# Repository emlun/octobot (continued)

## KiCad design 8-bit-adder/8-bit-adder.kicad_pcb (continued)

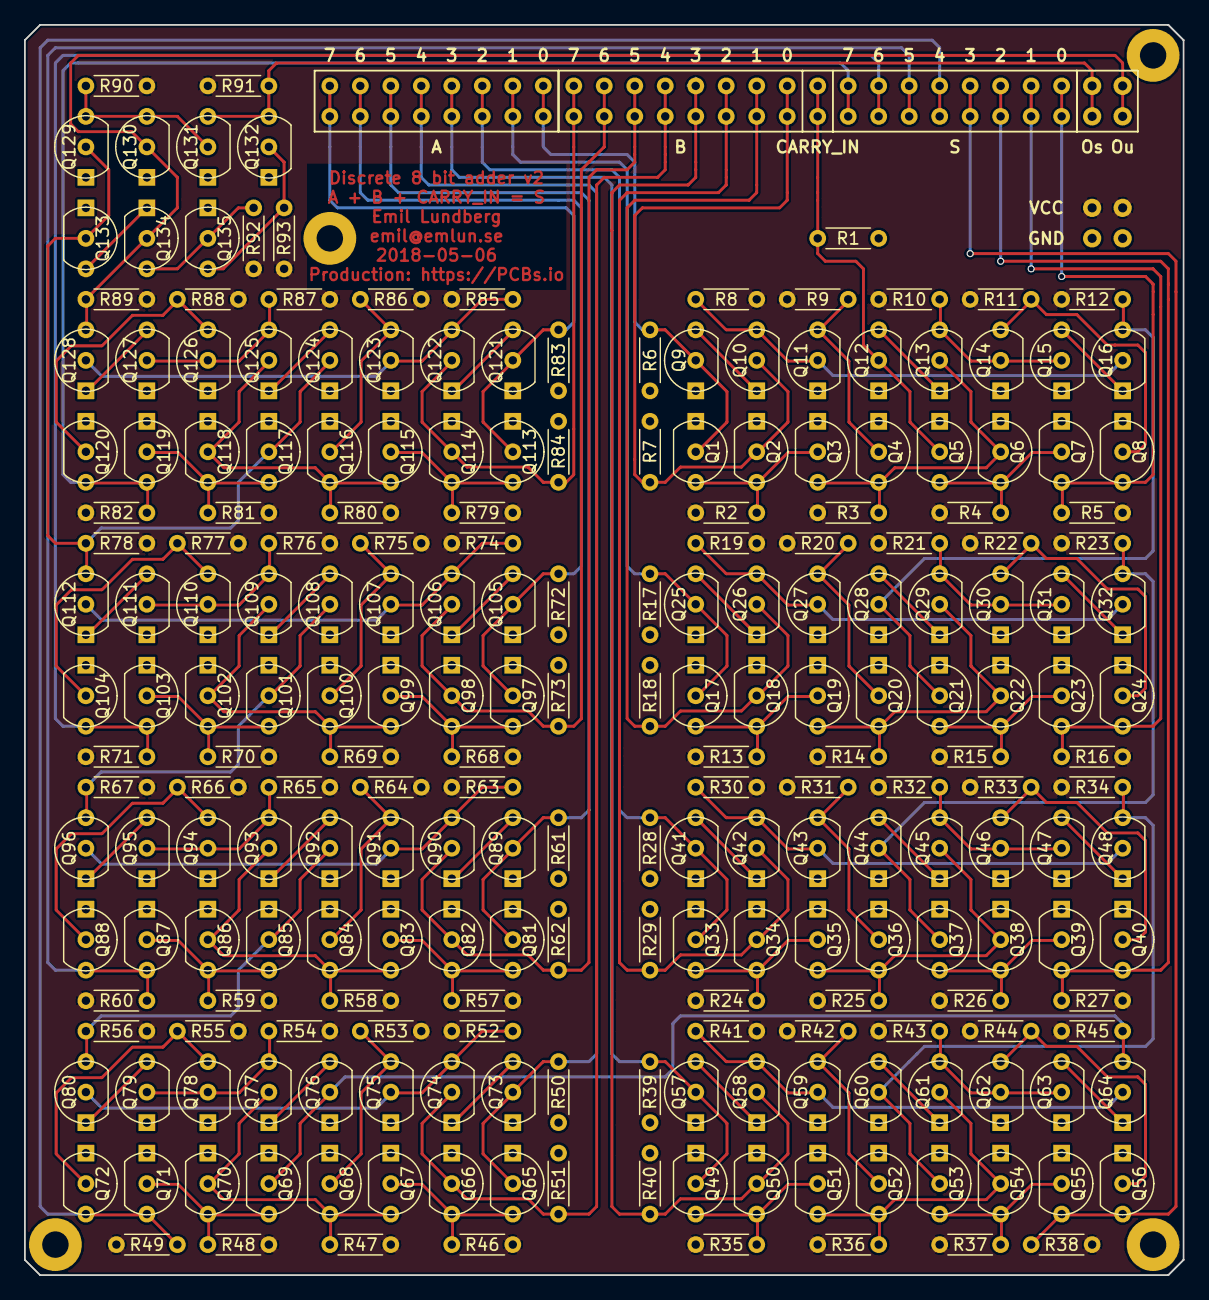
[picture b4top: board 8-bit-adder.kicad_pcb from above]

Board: 2 copper layers, 96.5 x 104.1 mm, 234 parts (0 on the bottom side), 120 nets.

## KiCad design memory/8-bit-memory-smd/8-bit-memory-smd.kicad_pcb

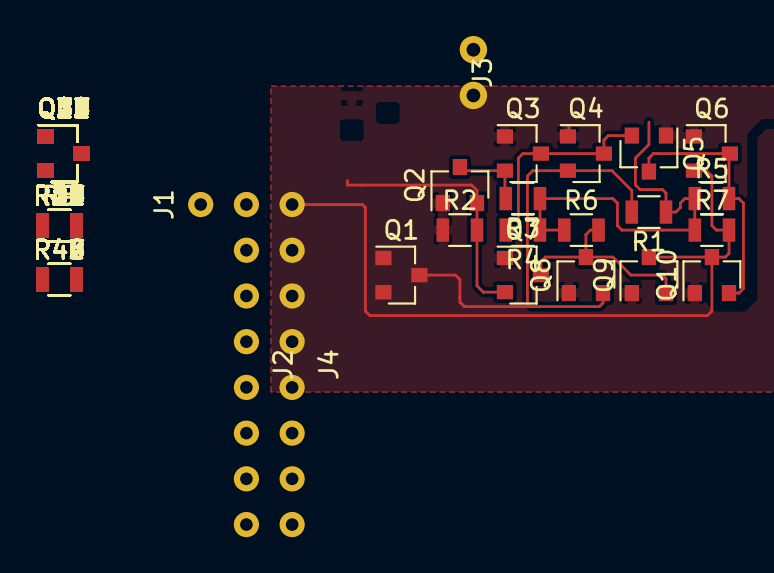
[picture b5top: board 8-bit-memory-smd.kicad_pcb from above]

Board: 2 copper layers, 126 parts (0 on the bottom side), 52 nets.

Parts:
J1: J1-1_bit_bus
J2, J4: J8-8_bit_bus_connector
J3: J2-2_pole_connector
Q1, Q2, Q3, Q4, Q5, Q6, Q7, Q8, Q9, Q10, Q11, Q12, Q13, Q14, Q15, Q16, Q17, Q18, Q19, Q20, Q21, Q22, Q23, Q24, Q25, Q26, Q27, Q28, Q29, Q30, Q31, Q32, Q33, Q34, Q35, Q36, Q37, Q38, Q39, Q40, Q41, Q42, Q43, Q44, Q45, Q46, Q47, Q48, Q49, Q50, Q51, Q52, Q53, Q54, Q55, Q56, Q57, Q58, Q59, Q60, Q61, Q62, Q63, Q64, Q65, Q66, Q67, Q68, Q69, Q70, Q71, Q72, Q73: 2N7000; SOT-23
R1, R2, R3, R4, R5, R6, R7, R8, R9, R10, R11, R12, R13, R14, R15, R16, R17, R18, R19, R20, R21, R22, R23, R24, R25, R26, R27, R28, R29, R30, R31, R32, R33, R34, R35, R36, R37, R38, R39, R40, R41, R42, R43, R44, R45, R46, R47, R48, R49: R; R_0805

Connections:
/I0: J2.0, Q2.2, Q7.2, R2.2
/I1: J2.1, Q11.2, Q16.2, R8.2
/I2: J2.2, Q20.2, Q25.2, R14.2
/I3: J2.3, Q29.2, Q34.2, R20.2
/I4: J2.4, Q38.2, Q43.2, R26.2
/I5: J2.5, Q47.2, Q52.2, R32.2
/I6: J2.6, Q56.2, Q61.2, R38.2
/I7: J2.7, Q65.2, Q70.2, R44.2
/O0: J4.0, Q6.2, Q9.3, Q10.3, R7.2
/O1: J4.1, Q15.2, Q18.3, Q19.3, R13.2
/O2: J4.2, Q24.2, Q27.3, Q28.3, R19.2
/O3: J4.3, Q33.2, Q36.3, Q37.3, R25.2
/O4: J4.4, Q42.2, Q45.3, Q46.3, R31.2
/O5: J4.5, Q51.2, Q54.3, Q55.3, R37.2
/O6: J4.6, Q60.2, Q63.3, Q64.3, R43.2
/O7: J4.7, Q69.2, Q72.3, Q73.3, R49.2
/W: J1.1, Q1.2
/notW: Q1.3, Q4.2, Q8.2, Q13.2, Q17.2, Q22.2, Q26.2, Q31.2, Q35.2, Q40.2, Q44.2, Q49.2, Q53.2, Q58.2, Q62.2, Q67.2, Q71.2, R1.2
GND: J3.1, Q1.1, Q2.1, Q3.1, Q4.1, Q5.1, Q6.1, Q7.1, Q8.1, Q9.1, Q10.1, Q11.1, Q12.1, Q13.1, Q14.1, Q15.1, Q16.1, Q17.1, Q18.1, Q19.1, Q20.1, Q21.1, Q22.1, Q23.1, Q24.1, Q25.1, Q26.1, Q27.1, Q28.1, Q29.1, Q30.1, Q31.1, Q32.1, Q33.1, Q34.1, Q35.1, Q36.1, Q37.1, Q38.1, Q39.1, Q40.1, Q41.1, Q42.1, Q43.1, Q44.1, Q45.1, Q46.1, Q47.1, Q48.1, Q49.1, Q50.1, Q51.1, Q52.1, Q53.1, Q54.1, Q55.1, Q56.1, Q57.1, Q58.1, Q59.1, Q60.1, Q61.1, Q62.1, Q63.1, Q64.1, Q65.1, Q66.1, Q67.1, Q68.1, Q69.1, Q70.1, Q71.1, Q72.1, Q73.1, R2.1, R8.1, R14.1, R20.1, R26.1, R32.1, R38.1, R44.1
unnamed: Q2.3, Q3.2, R3.2
unnamed: Q3.3, Q4.3, Q5.2, R4.2
unnamed: Q7.3, Q8.3, Q9.2, R6.2
unnamed: Q5.3, Q6.3, Q10.2, R5.2
unnamed: Q11.3, Q12.2, R9.2
unnamed: Q12.3, Q13.3, Q14.2, R10.2
unnamed: Q14.3, Q15.3, Q19.2, R11.2
unnamed: Q16.3, Q17.3, Q18.2, R12.2
unnamed: Q20.3, Q21.2, R15.2
unnamed: Q21.3, Q22.3, Q23.2, R16.2
unnamed: Q23.3, Q24.3, Q28.2, R17.2
unnamed: Q25.3, Q26.3, Q27.2, R18.2
unnamed: Q29.3, Q30.2, R21.2
unnamed: Q30.3, Q31.3, Q32.2, R22.2
unnamed: Q32.3, Q33.3, Q37.2, R23.2
unnamed: Q34.3, Q35.3, Q36.2, R24.2
unnamed: Q38.3, Q39.2, R27.2
unnamed: Q39.3, Q40.3, Q41.2, R28.2
unnamed: Q41.3, Q42.3, Q46.2, R29.2
unnamed: Q43.3, Q44.3, Q45.2, R30.2
unnamed: Q47.3, Q48.2, R33.2
unnamed: Q48.3, Q49.3, Q50.2, R34.2
unnamed: Q50.3, Q51.3, Q55.2, R35.2
unnamed: Q52.3, Q53.3, Q54.2, R36.2
unnamed: Q56.3, Q57.2, R39.2
unnamed: Q57.3, Q58.3, Q59.2, R40.2
unnamed: Q59.3, Q60.3, Q64.2, R41.2
unnamed: Q61.3, Q62.3, Q63.2, R42.2
unnamed: Q65.3, Q66.2, R45.2
unnamed: Q66.3, Q67.3, Q68.2, R46.2
unnamed: Q68.3, Q69.3, Q73.2, R47.2
unnamed: Q70.3, Q71.3, Q72.2, R48.2
VCC: J3.2, R1.1, R3.1, R4.1, R5.1, R6.1, R7.1, R9.1, R10.1, R11.1, R12.1, R13.1, R15.1, R16.1, R17.1, R18.1, R19.1, R21.1, R22.1, R23.1, R24.1, R25.1, R27.1, R28.1, R29.1, R30.1, R31.1, R33.1, R34.1, R35.1, R36.1, R37.1, R39.1, R40.1, R41.1, R42.1, R43.1, R45.1, R46.1, R47.1, R48.1, R49.1

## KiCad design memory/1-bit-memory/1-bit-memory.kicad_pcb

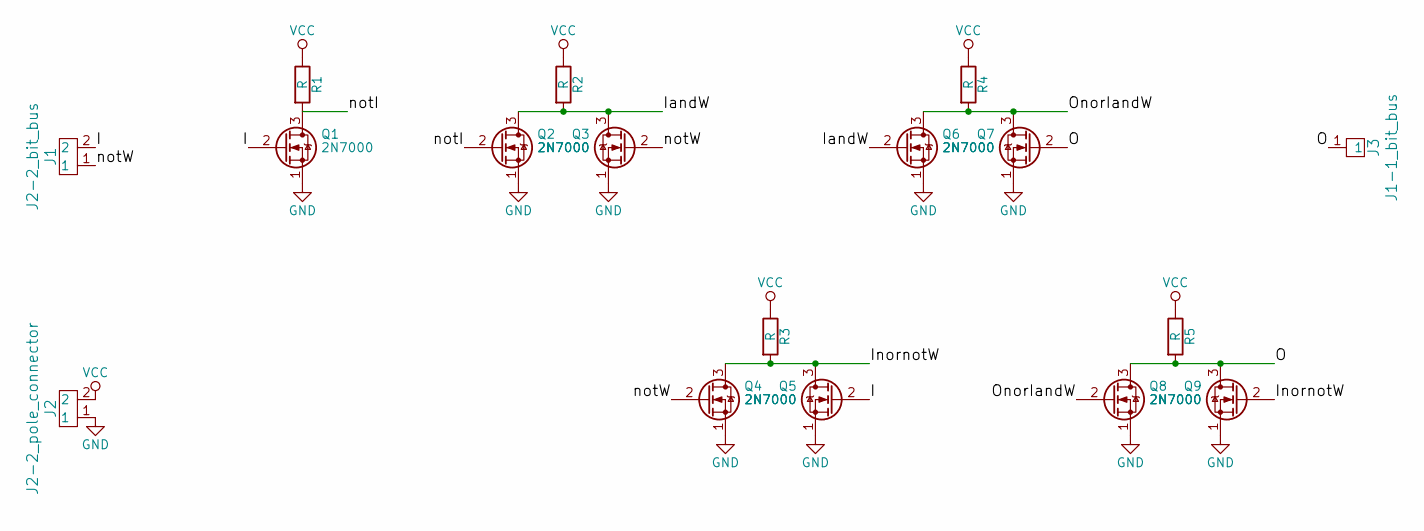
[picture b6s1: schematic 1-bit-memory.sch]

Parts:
J1: J2-2_bit_bus; J2-2_pole_connector
J2: J2-2_pole_connector
J3: J1-1_bit_bus
Q1, Q2, Q3, Q4, Q5, Q6, Q7, Q8, Q9: 2N7000; SOT-23
R1, R2, R3, R4, R5: R; R_0805

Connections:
/I: J1.2, Q1.2 (G), Q5.2 (G)
/IandW: Q2.3 (D), Q3.3 (D), Q6.2 (G), R2.2
/InornotW: Q4.3 (D), Q5.3 (D), Q9.2 (G), R3.2
/O: J3.1, Q7.2 (G), Q8.3 (D), Q9.3 (D), R5.2
/OnorIandW: Q6.3 (D), Q7.3 (D), Q8.2 (G), R4.2
/notI: Q1.3 (D), Q2.2 (G), R1.2
/notW: J1.1, Q3.2 (G), Q4.2 (G)
GND: J2.1, Q1.1 (S), Q2.1 (S), Q3.1 (S), Q4.1 (S), Q5.1 (S), Q6.1 (S), Q7.1 (S), Q8.1 (S), Q9.1 (S)
VCC: J2.2, R1.1, R2.1, R3.1, R4.1, R5.1

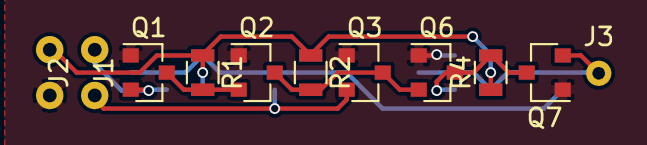
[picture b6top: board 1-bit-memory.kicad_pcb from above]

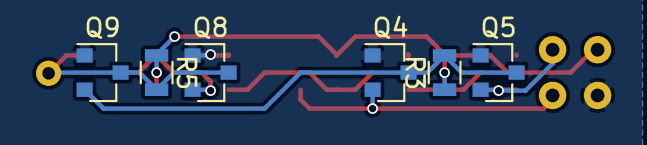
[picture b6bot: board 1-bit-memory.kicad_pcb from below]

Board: 2 copper layers, 17 parts (6 on the bottom side), 9 nets.

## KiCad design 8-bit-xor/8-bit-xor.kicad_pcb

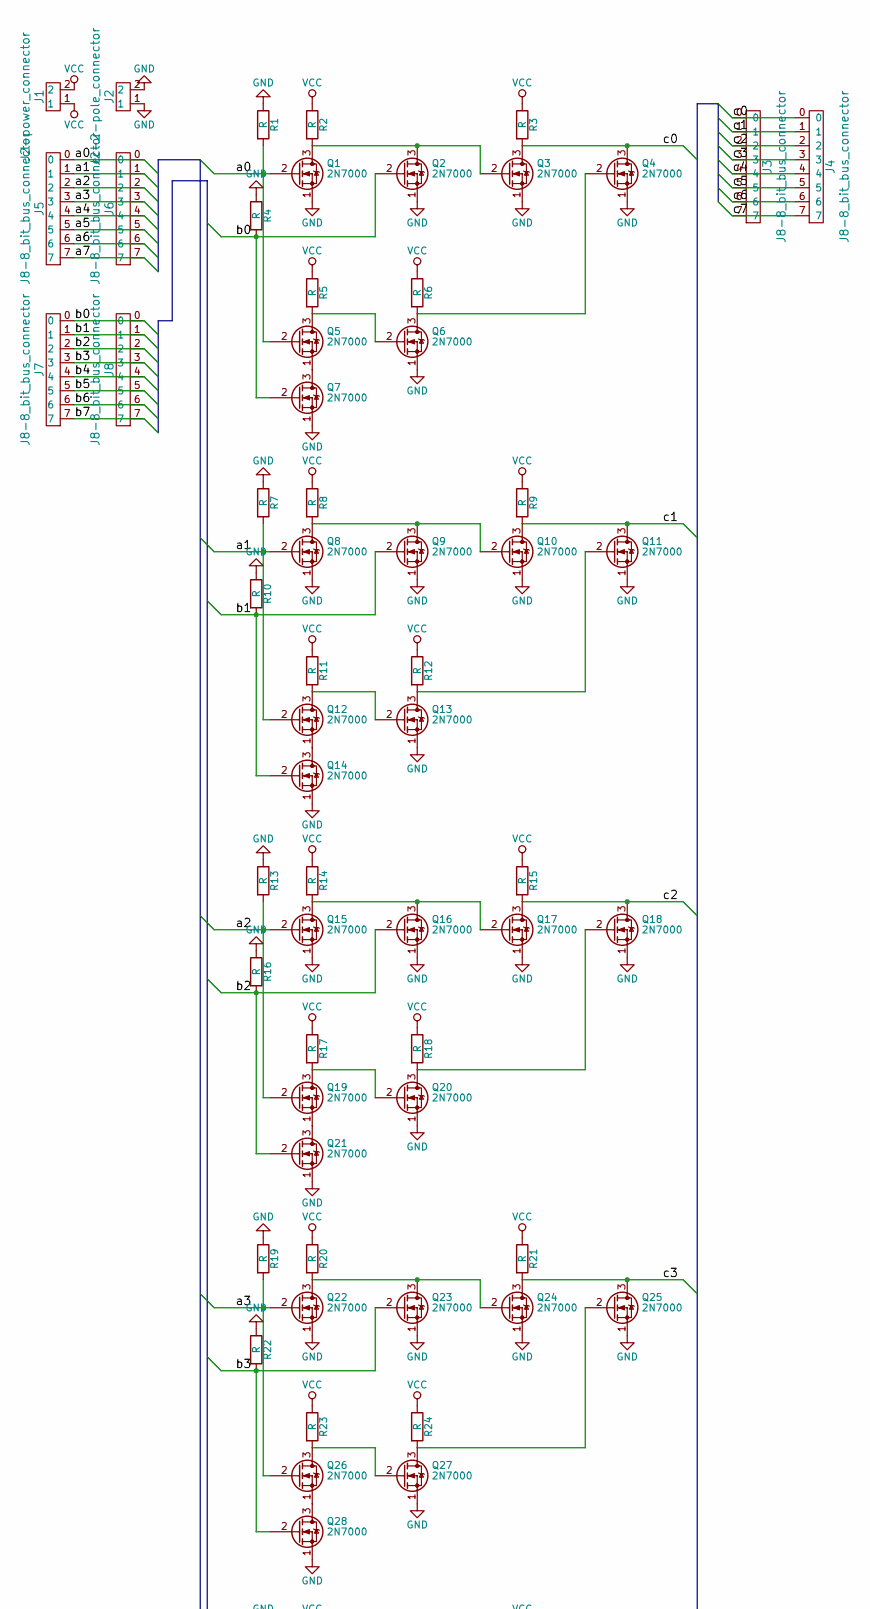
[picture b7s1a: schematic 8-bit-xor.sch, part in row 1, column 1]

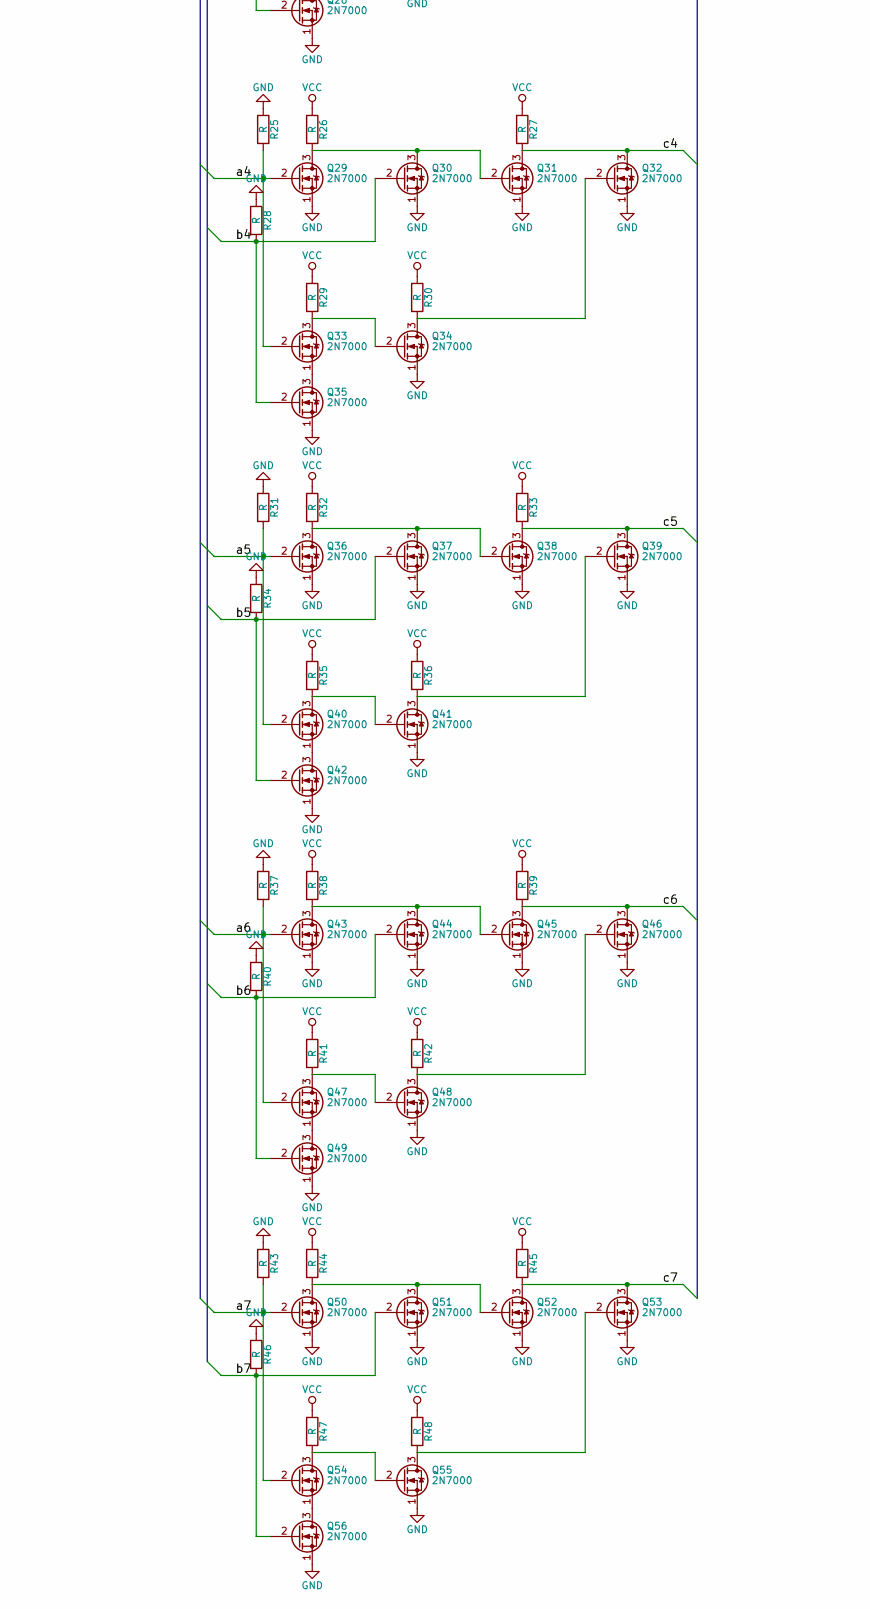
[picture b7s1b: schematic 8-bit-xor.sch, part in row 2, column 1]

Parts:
J1: J2-power_connector; J2-2_pole_connector
J2: J2-2-pole_connector; J2-2_pole_connector
J3, J4, J5, J6, J7, J8: J8-8_bit_bus_connector
Q1, Q2, Q3, Q4, Q5, Q6, Q7, Q8, Q9, Q10, Q11, Q12, Q13, Q14, Q15, Q16, Q17, Q18, Q19, Q20, Q21, Q22, Q23, Q24, Q25, Q26, Q27, Q28, Q29, Q30, Q31, Q32, Q33, Q34, Q35, Q36, Q37, Q38, Q39, Q40, Q41, Q42, Q43, Q44, Q45, Q46, Q47, Q48, Q49, Q50, Q51, Q52, Q53, Q54, Q55, Q56: 2N7000; TO-92_Molded_Wide_Inline
R1, R2, R3, R4, R5, R6, R7, R8, R9, R10, R11, R12, R13, R14, R15, R16, R17, R18, R19, R20, R21, R22, R23, R24, R25, R26, R27, R28, R29, R30, R31, R32, R33, R34, R35, R36, R37, R38, R39, R40, R41, R42, R43, R44, R45, R46, R47, R48: R; R_Axial_DIN0204_L3.6mm_D1.6mm_P5.08mm_Horizontal

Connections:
/a0: J5.0, J6.0, Q1.2 (G), Q5.2 (G), R1.2
/a1: J5.1, J6.1, Q8.2 (G), Q12.2 (G), R7.2
/a2: J5.2, J6.2, Q15.2 (G), Q19.2 (G), R13.2
/a3: J5.3, J6.3, Q22.2 (G), Q26.2 (G), R19.2
/a4: J5.4, J6.4, Q29.2 (G), Q33.2 (G), R25.2
/a5: J5.5, J6.5, Q36.2 (G), Q40.2 (G), R31.2
/a6: J5.6, J6.6, Q43.2 (G), Q47.2 (G), R37.2
/a7: J5.7, J6.7, Q50.2 (G), Q54.2 (G), R43.2
/b0: J7.0, J8.0, Q2.2 (G), Q7.2 (G), R4.2
/b1: J7.1, J8.1, Q9.2 (G), Q14.2 (G), R10.2
/b2: J7.2, J8.2, Q16.2 (G), Q21.2 (G), R16.2
/b3: J7.3, J8.3, Q23.2 (G), Q28.2 (G), R22.2
/b4: J7.4, J8.4, Q30.2 (G), Q35.2 (G), R28.2
/b5: J7.5, J8.5, Q37.2 (G), Q42.2 (G), R34.2
/b6: J7.6, J8.6, Q44.2 (G), Q49.2 (G), R40.2
/b7: J7.7, J8.7, Q51.2 (G), Q56.2 (G), R46.2
/c0: J3.0, J4.0, Q3.3 (D), Q4.3 (D), R3.2
/c1: J3.1, J4.1, Q10.3 (D), Q11.3 (D), R9.2
/c2: J3.2, J4.2, Q17.3 (D), Q18.3 (D), R15.2
/c3: J3.3, J4.3, Q24.3 (D), Q25.3 (D), R21.2
/c4: J3.4, J4.4, Q31.3 (D), Q32.3 (D), R27.2
/c5: J3.5, J4.5, Q38.3 (D), Q39.3 (D), R33.2
/c6: J3.6, J4.6, Q45.3 (D), Q46.3 (D), R39.2
/c7: J3.7, J4.7, Q52.3 (D), Q53.3 (D), R45.2
GND: J2.1, J2.2, Q1.1 (S), Q2.1 (S), Q3.1 (S), Q4.1 (S), Q6.1 (S), Q7.1 (S), Q8.1 (S), Q9.1 (S), Q10.1 (S), Q11.1 (S), Q13.1 (S), Q14.1 (S), Q15.1 (S), Q16.1 (S), Q17.1 (S), Q18.1 (S), Q20.1 (S), Q21.1 (S), Q22.1 (S), Q23.1 (S), Q24.1 (S), Q25.1 (S), Q27.1 (S), Q28.1 (S), Q29.1 (S), Q30.1 (S), Q31.1 (S), Q32.1 (S), Q34.1 (S), Q35.1 (S), Q36.1 (S), Q37.1 (S), Q38.1 (S), Q39.1 (S), Q41.1 (S), Q42.1 (S), Q43.1 (S), Q44.1 (S), Q45.1 (S), Q46.1 (S), Q48.1 (S), Q49.1 (S), Q50.1 (S), Q51.1 (S), Q52.1 (S), Q53.1 (S), Q55.1 (S), Q56.1 (S), R1.1, R4.1, R7.1, R10.1, R13.1, R16.1, R19.1, R22.1, R25.1, R28.1, R31.1, R34.1, R37.1, R40.1, R43.1, R46.1
unnamed: Q1.3 (D), Q2.3 (D), Q3.2 (G), R2.2
unnamed: Q4.2 (G), Q6.3 (D), R6.2
unnamed: Q5.1 (S), Q7.3 (D)
unnamed: Q5.3 (D), Q6.2 (G), R5.2
unnamed: Q8.3 (D), Q9.3 (D), Q10.2 (G), R8.2
unnamed: Q11.2 (G), Q13.3 (D), R12.2
unnamed: Q12.1 (S), Q14.3 (D)
unnamed: Q12.3 (D), Q13.2 (G), R11.2
unnamed: Q15.3 (D), Q16.3 (D), Q17.2 (G), R14.2
unnamed: Q18.2 (G), Q20.3 (D), R18.2
unnamed: Q19.1 (S), Q21.3 (D)
unnamed: Q19.3 (D), Q20.2 (G), R17.2
unnamed: Q22.3 (D), Q23.3 (D), Q24.2 (G), R20.2
unnamed: Q25.2 (G), Q27.3 (D), R24.2
unnamed: Q26.1 (S), Q28.3 (D)
unnamed: Q26.3 (D), Q27.2 (G), R23.2
unnamed: Q29.3 (D), Q30.3 (D), Q31.2 (G), R26.2
unnamed: Q32.2 (G), Q34.3 (D), R30.2
unnamed: Q33.1 (S), Q35.3 (D)
unnamed: Q33.3 (D), Q34.2 (G), R29.2
unnamed: Q36.3 (D), Q37.3 (D), Q38.2 (G), R32.2
unnamed: Q39.2 (G), Q41.3 (D), R36.2
unnamed: Q40.1 (S), Q42.3 (D)
unnamed: Q40.3 (D), Q41.2 (G), R35.2
unnamed: Q43.3 (D), Q44.3 (D), Q45.2 (G), R38.2
unnamed: Q46.2 (G), Q48.3 (D), R42.2
unnamed: Q47.1 (S), Q49.3 (D)
unnamed: Q47.3 (D), Q48.2 (G), R41.2
unnamed: Q50.3 (D), Q51.3 (D), Q52.2 (G), R44.2
unnamed: Q53.2 (G), Q55.3 (D), R48.2
unnamed: Q54.1 (S), Q56.3 (D)
unnamed: Q54.3 (D), Q55.2 (G), R47.2
VCC: J1.1, J1.2, R2.1, R3.1, R5.1, R6.1, R8.1, R9.1, R11.1, R12.1, R14.1, R15.1, R17.1, R18.1, R20.1, R21.1, R23.1, R24.1, R26.1, R27.1, R29.1, R30.1, R32.1, R33.1, R35.1, R36.1, R38.1, R39.1, R41.1, R42.1, R44.1, R45.1, R47.1, R48.1

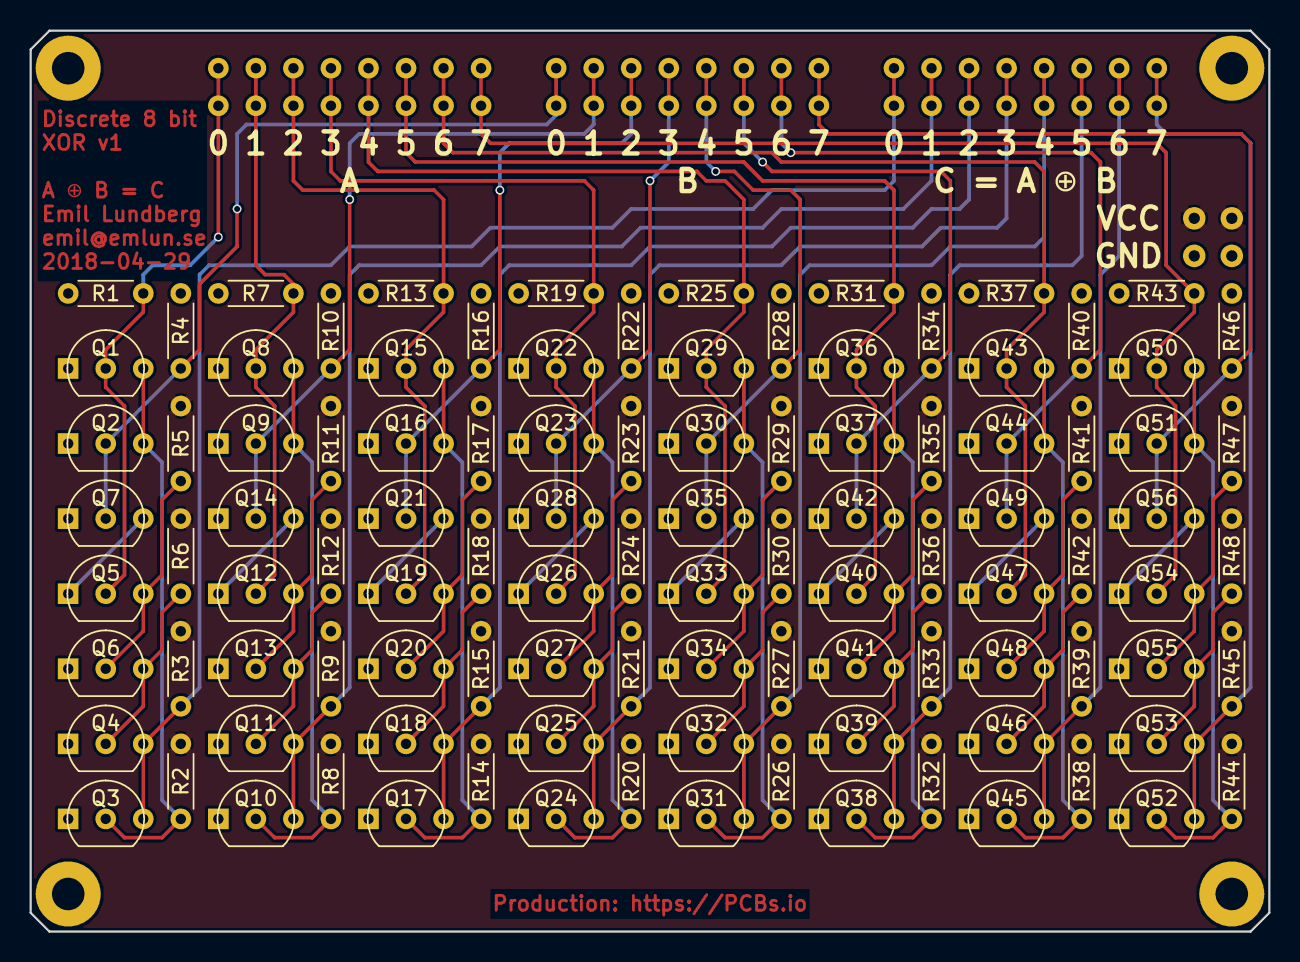
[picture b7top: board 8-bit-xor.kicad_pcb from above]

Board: 2 copper layers, 83.8 x 61.0 mm, 112 parts (0 on the bottom side), 58 nets.

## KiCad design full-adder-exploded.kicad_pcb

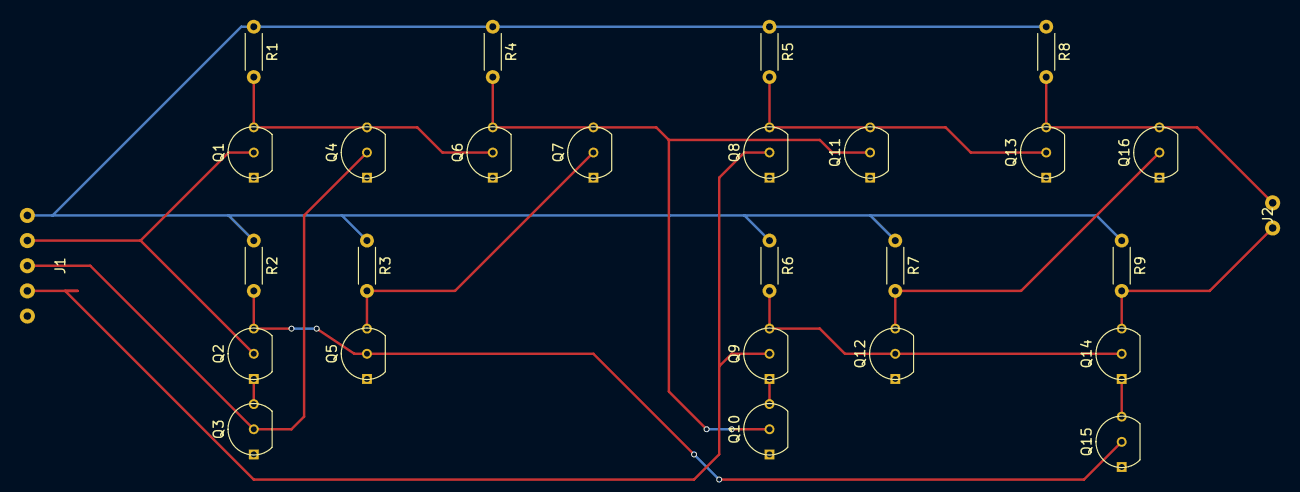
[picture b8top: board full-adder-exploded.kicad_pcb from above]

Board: 2 copper layers, 27 parts (0 on the bottom side), 16 nets.

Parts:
J1: J5-5_pole_connector
J2: J2-2_pole_connector
Q1, Q2, Q3, Q4, Q5, Q6, Q7, Q8, Q9, Q10, Q11, Q12, Q13, Q14, Q15, Q16: 2N7000; TO-92_Molded_Wide_Inline
R1, R2, R3, R4, R5, R6, R7, R8, R9: 1M; R_Axial_DIN0204_L3.6mm_D1.6mm_P5.08mm_Horizontal

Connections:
/A: J1.2, Q1.2, Q2.2
/AandB: Q5.3, Q7.2, R3.2
/AnandB: Q2.3, Q5.2, Q15.2, R2.2
/AnorB: Q1.3, Q4.3, Q6.2, R1.2
/AnorBnorAandB: Q6.3, Q7.3, Q10.2, Q11.2, R4.2
/B: J1.3, Q3.2, Q4.2
/C: J1.4, Q8.2, Q9.2
/CandD: Q12.3, Q16.2, R7.2
/Carry: J2.2, Q14.3, R9.2
/CnandD: Q9.3, Q12.2, Q14.2, R6.2
/CnorD: Q8.3, Q11.3, Q13.2, R5.2
/CnorDnorCandD: J2.1, Q13.3, Q16.3, R8.2
unnamed: Q2.1, Q3.3
unnamed: Q9.1, Q10.3
unnamed: Q14.1, Q15.3
VCC: J1.1, R1.1, R2.1, R3.1, R4.1, R5.1, R6.1, R7.1, R8.1, R9.1

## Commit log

2017-09-17 Initial commit: Add full adder schematics
2017-09-17 Add 8 bit adder schematics
2017-09-17 Fix pins on component J5-5_pole_connector
2017-09-17 Add .gitignore
2017-09-17 Add license
2017-09-17 Add README
2017-09-17 Fix library paths and add missing resistor annotations
2017-09-17 Generate gerber files for 8 bit adder v1
2017-09-17 Add carry input to 8 bit adder
2017-09-17 Generate drill file correctly
2018-04-29 Commit old changes
2018-04-30 Add component J2-2-pole_connector
2018-04-30 Tweak labels on TO-92 footprint
2018-04-30 Tweak label on resistor footprint
2018-04-30 Add 8-bit XOR schematics
2018-05-01 Add memory schematics
2018-05-01 Rename 8-bit-memory project to 8-bit-memory-smd
2018-05-01 Copy 8-bit-memory-smd project to 8-bit-memory-tht
2018-05-01 Add double versions of bus connectors
2018-05-01 Fix center of TO-92 footprint
2018-05-01 Finish THT memory board layout
2018-05-01 Add Gerber files for 8-bit-memory-tht
2018-05-06 Fix pin types of power connector component
2018-05-06 Regenerate 8-bit-adder plot files
2018-05-06 Update adder circuit to revision 2
2018-05-06 Add make-pcbs-io-tarball.sh
2018-06-24 Add footprints used by Crazy Circuit Conundrum for Midnight Sun CTF
2018-06-30 Add outline around J1x2-double_1_bit_bus footprint
2018-06-30 Migrate TO-92 Molded Wide Inline footprint
2018-06-30 Add battery holder footprints
2018-06-30 Add sketch of bus selector circuit
2018-06-30 Add symbol for memory circuit
2018-06-30 Add THT memory circuit v2
2018-06-30 Add symbol for XOR circuit
2018-06-30 Rescue old components
2018-06-30 Add symbol for adder circuit
2018-06-30 Prettify PWR symbol
2018-07-19 Additional tweaks to bus selector circuit diagram
2018-07-19 Finish bus selector connection diagram
2018-07-19 Add test program for XOR circuit
2018-07-19 Rearrange pins in adder test to allow live reprogramming
2018-07-19 Ignore archives
2018-07-19 Add test program for memory circuit
2018-07-19 Add adder test sketch
2018-07-19 Cosmetic tweaks to footprint library
2018-07-19 Greatly simplify bus selector circuit
2018-07-19 Print adder test results to serial monitor
2018-07-19 Add Gerber files for bus selector
2018-07-19 Add setup instructions to adder test program
2018-07-19 Add draft of bus selector PCB layout
2018-07-19 Finish PCB layout of bus selector
2018-07-19 Add 8 bit bitwise logic circuit
2018-07-19 Add Gerber files for 8-bit bitwise logic circuit
2018-07-19 Add pull-down resistors to bus selector
2018-07-19 Fix alignment of PWR-2_pole_power_connector component
2018-07-29 Add pull-down resistors to bus selector inputs
2018-07-30 Update power connector component in bitwise logic schematic
2018-07-31 Fix pin types in memory circuit symbol
2018-07-31 Add bitwise logic component symbol
2018-07-31 Add bus selector symbol
2018-07-31 Add 8-input NOR symbol
2018-08-01 Add footprint for bus selector symbol
2018-08-01 Add footprint for adder symbol
2018-08-01 Add footprint for bitwise logic symbol
2018-08-01 Add footprint for xor logic symbol
2018-08-01 Add double 3- and 4-bit bus connector footprints
2018-08-01 Remove endianness indicators from 8-bit bus connector footprint
2018-08-01 Add footprint for 8-input NOR symbol
2018-08-01 Fix reference texts in bus connector footprints
2018-08-02 Flip orientation of XOR subcircuit buses in ALU control unit
    This makes routing these buses easier, while not affecting the output.
2018-08-02 Unify pin header footprints at 1,524mm pads with 0,762mm hole
2018-08-02 Unify pin header footprints at 1,4mm pads with 0,7mm hole
2018-08-02 Add silkscreen outline to bitwise logic circuit footprint
2018-08-02 Add silkscreen outline to adder circuit footprint
2018-08-02 Add silkscreen outline to xor circuit footprint
2018-08-02 Add silkscreen outline to bus selector footprint
2018-08-02 Add ALU control unit schematic
2018-08-02 Add silkscreen outline to 8-input NOR circuit footprint
2018-08-02 Remove extraneous text from xor circuit footprint
2018-08-02 Rearrange bus wiring in ALU control unit schematic
2018-08-02 Add first draft of ALU control unit PCB layout
2018-08-02 Use rectangular pads for GND pins
2018-08-02 Replace footprint J2x2-double_2_pole_connector with PWR-double_2_pole_power_connector
2018-08-02 Fix 3D settings for new pin header footprints
2018-08-02 Add 3D settings for 1x2 pin header footprint
2018-08-02 Hide reference on J1x2 footprint by default
2018-08-02 Touch up ALU control unit PCB layout
2018-08-02 Fix reference text in 8-input NOR footprint
2018-08-02 Center label on XOR circuit footprint
2018-08-03 Add test program for 8-input NOR circuit
2018-08-03 Rearrange 8-input NOR footprint to match the working prototype
2018-08-03 Assign the unassigned ALU op code to echo operand A
2018-08-03 Update ALU PCB layout with new operation code
2018-08-03 Add pull-down resistors to ALU control unit inputs
2018-08-03 Wire up ALU pull-down resistors
2018-08-03 Cleanup tracks and vias
2018-08-03 Fix a track too close to a mounting hole
2018-08-03 Make pull-down resistor connections visible on front side
2018-08-03 Add VCC and GND labels to ALU control unit PCB
2018-08-05 Redefine pin 15 as SIGNED_OVERFLOW_PIN
2018-08-05 Use const int for pin number definitions
2018-08-05 Fix compiler warnings
2018-08-05 Add tests for behaviour of signed number addition
2018-08-05 Make adder test program work with 1M resistors
2018-08-05 Print incorrect results in adder test
2018-08-05 Add draft of test program for bus selector
2019-05-11 Fix order of boolean operations in opcodes label
2019-05-11 Add ? to zero detector subsystem label
2019-05-11 Add test program for bitwise logic board
